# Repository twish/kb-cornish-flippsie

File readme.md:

# cornish_flippsie

40 key split keyboard that uses a flipped PCB, ProMicro controller, Gateron Low Profile Switches and is Vial enabled.  

This is a first generation of a custom built keyboard, so there are a lot of things that works but 
could be done a lot better.

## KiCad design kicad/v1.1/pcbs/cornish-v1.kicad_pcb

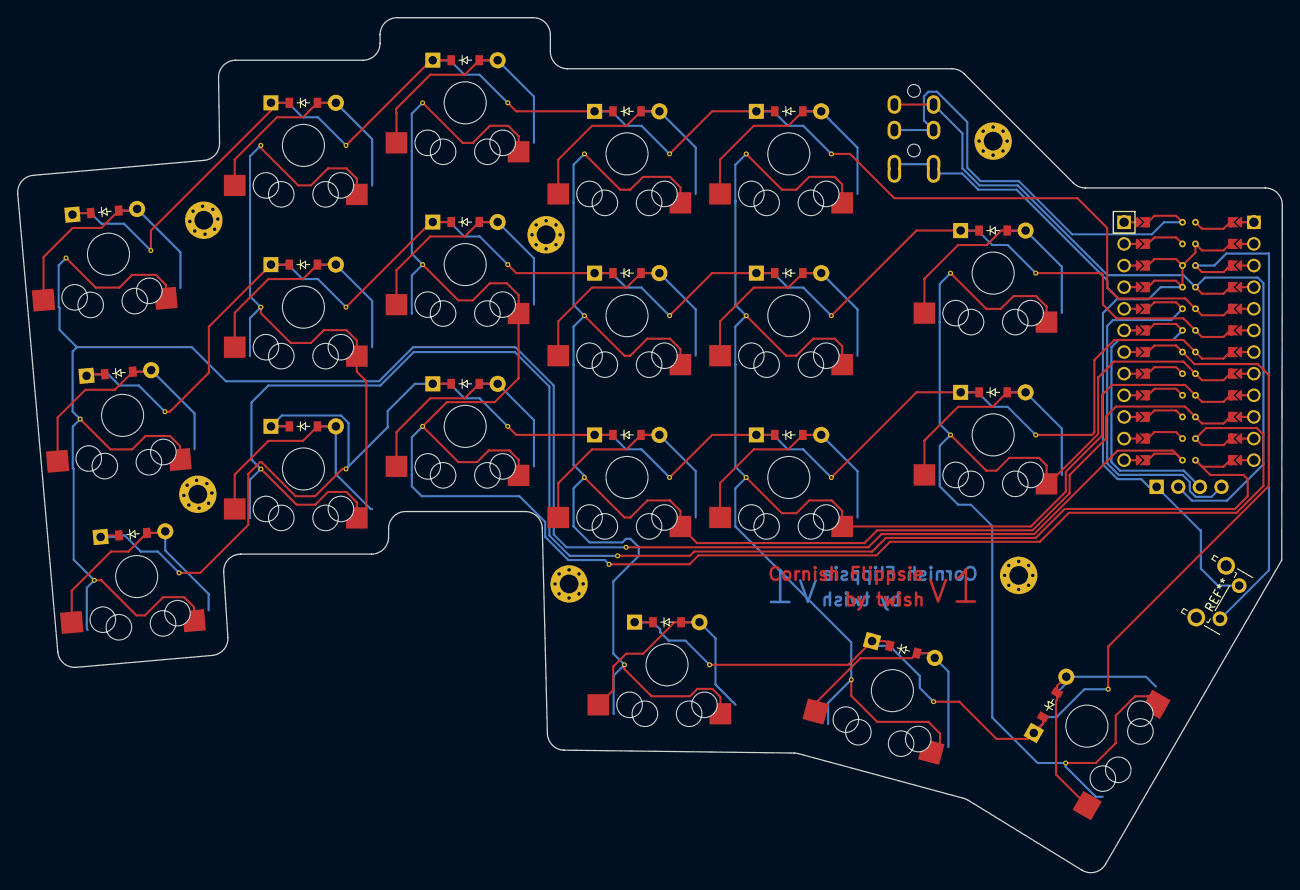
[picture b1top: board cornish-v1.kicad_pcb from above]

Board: 2 copper layers, 148.5 x 100.4 mm, 49 parts (0 on the bottom side), 35 nets.

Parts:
D1, D2, D3, D4, D5, D6, D7, D8, D9, D10, D11, D12, D13, D14, D15, D16, D17, D18, D19, D20: ComboDiode
OLED1: OLED; OLED_headers
S1, S2, S3, S4, S5, S6, S7, S8, S9, S10, S11, S12, S13, S14, S15, S16, S17, S18, S19, S20: ks33; Gateron-Low-Profile-ks-33
TRRS1: TRRS-PJ-320A-dual
_41: ProMicro
_42, _43, _44, _45, _46, _47: MountingHole_2.2mm_M2_Pad_Via

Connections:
GND: OLED1.1, TRRS1.1, TRRS1.2, _41.2, _41.21, _41.22
P1: TRRS1.3, _41.24
P2: OLED1.4, _41.20
P3: OLED1.3, _41.19
P4: D16.1, D17.1, D18.1, _41.18
P9: S1.1, S2.1, S3.1, _41.13
P10: S4.1, S5.1, S6.1, _41.12
P14: S10.1, S11.1, S12.1, S16.1, _41.10
P15: S13.1, S14.1, S15.1, S17.1, _41.9
P16: S7.1, S8.1, S9.1, _41.11
P18: S18.1, S19.1, S20.1, _41.8
P19: D1.1, D4.1, D7.1, D10.1, D13.1, D19.1, _41.7
P20: D2.1, D5.1, D8.1, D11.1, D14.1, D20.1, _41.6
P21: D3.1, D6.1, D9.1, D12.1, D15.1, _41.5
VCC: OLED1.2, TRRS1.4, _41.4
index2_bottom: D13.2, S13.2
index2_home: D14.2, S14.2
index2_top: D15.2, S15.2
index_bottom: D10.2, S10.2
index_home: D11.2, S11.2
index_top: D12.2, S12.2
layer_cluster: D17.2, S17.2
media_one: D19.2, S19.2
media_two: D20.2, S20.2
middle_bottom: D7.2, S7.2
middle_home: D8.2, S8.2
middle_top: D9.2, S9.2
mod_cluster: D16.2, S16.2
pinky_bottom: D1.2, S1.2
pinky_home: D2.2, S2.2
pinky_top: D3.2, S3.2
ring_bottom: D4.2, S4.2
ring_home: D5.2, S5.2
ring_top: D6.2, S6.2
space_cluster: D18.2, S18.2

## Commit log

2024-03-10 v1.0
2024-03-17 v1.1 and case
2024-03-24 updated to v1.2 with correct pads for sockets
2024-03-24 added qmk config
2024-03-31 updated qmk firmware with working oled, started on vial
2024-03-31 updated to working vial
2024-04-01 updated keymap to better reflect vial map
2024-04-06 restructured repo
2024-04-06 cleaned up repo
2024-04-06 some more cleanp;
2024-04-06 start on v2
